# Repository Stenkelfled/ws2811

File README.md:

# ws2811
WS2811 LED microcontroller driver with USB-connection and UserInterface for PC

Another Project for a WS2811 LED-strip. The clue here is, that the controller board is accessible via USB and that you can control the LEDs from you PC/Laptop.

Includes:
- Electronics design with ATXMEGA
- code for the xmega
- an UserInterface for a pc to communicate with the microcontroller written with Qt

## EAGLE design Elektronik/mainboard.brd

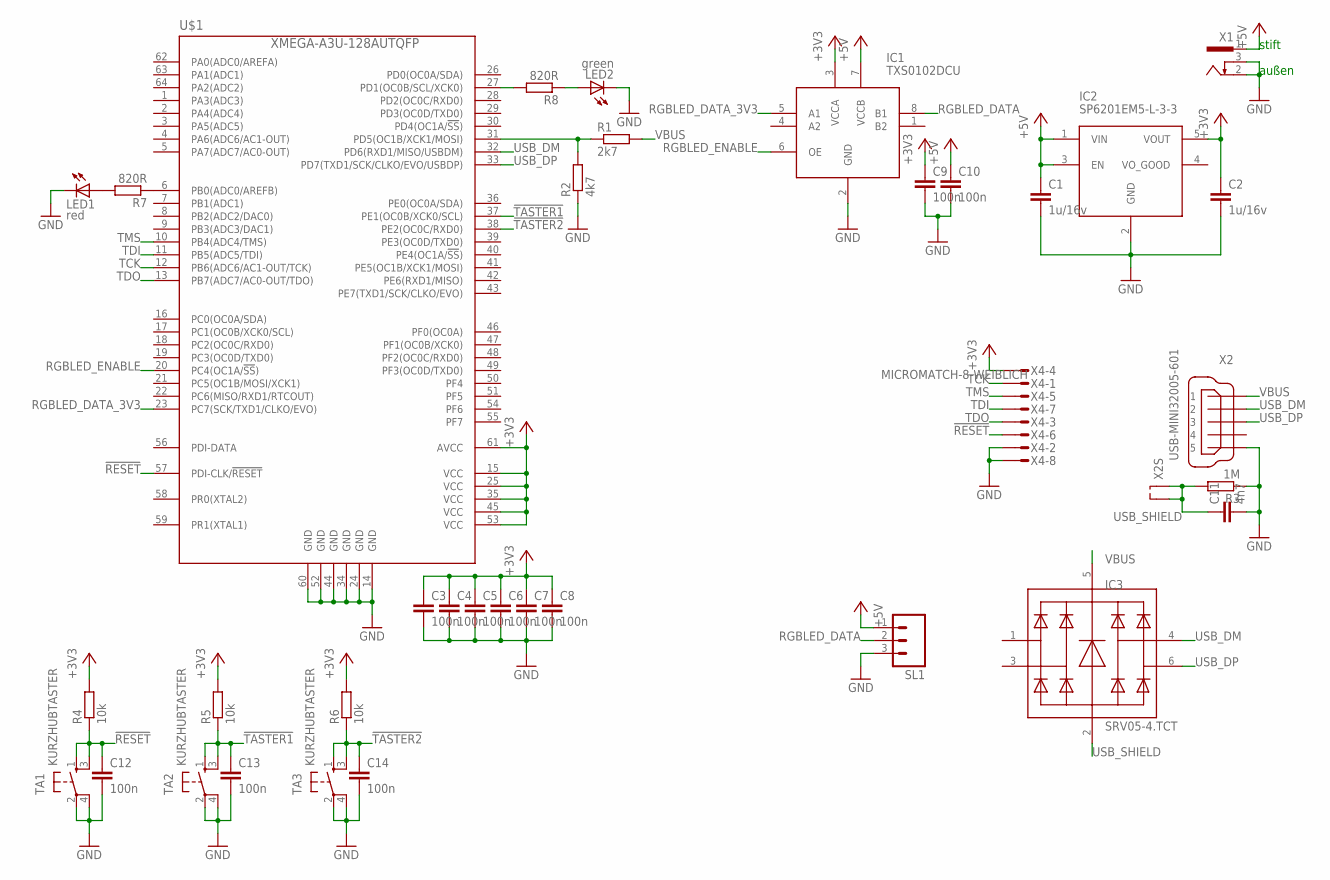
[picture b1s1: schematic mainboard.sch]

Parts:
C1, C2: 1u/16v; C0603
C3, C4, C5, C6, C7, C8, C9, C10, C12, C13, C14: 100n; C0603
C11: 4n7; C0603
IC1: TXS0102DCU; DCU8
IC2: SP6201EM5-L-3-3; SOT23-5
IC3: SRV05-4.TCT; SOT23-6
LED1: red; CHIPLED_0603
LED2: green; CHIPLED_0603
R1: 2k7; R0603
R2: 4k7; R0603
R3: 1M; R0603
R4, R5, R6: 10k; R0603
R7, R8: 820R; R0603
SL1: M03; 03P
TA1, TA2, TA3: KURZHUBTASTER; TA93XX
U$1: XMEGA-A3U-128AUTQFP; TQFP64
X1: 733980-62
X2: USB-MINI32005-601; 32005-601
X4: MICROMATCH-8-WEIBLICH; MICROMATCH-8

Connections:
!RESET!: C12.1, R4.1, TA1.1 (S), TA1.3 (S1), U$1.57 (PDI-CLK/!RESET), X4.6
!TASTER1!: C13.1, R5.1, TA2.1 (S), TA2.3 (S1), U$1.37 (PE1(OC0B/XCK0/SCL))
!TASTER2!: C14.1, R6.1, TA3.1 (S), TA3.3 (S1), U$1.38 (PE2(OC0C/RXD0))
+3V3: C2.1, C3.1, C4.1, C5.1, C6.1, C7.1, C8.1, C9.1, IC1.3 (VCCA), IC2.5 (VOUT), R4.2, R5.2, R6.2, U$1.15 (VCC), U$1.25 (VCC), U$1.35 (VCC), U$1.45 (VCC), U$1.53 (VCC), U$1.61 (AVCC), X4.4
+5V: C1.1, C10.1, IC1.7 (VCCB), IC2.1 (VIN), IC2.3 (EN), SL1.1, X1.1
GND: C1.2, C2.2, C3.2, C4.2, C5.2, C6.2, C7.2, C8.2, C9.2, C10.2, C11.2, C12.2, C13.2, C14.2, IC1.2 (GND), IC2.2 (GND), LED1.C, LED2.C, R2.1, R3.1, SL1.3, TA1.2, TA1.4 (P1), TA2.2, TA2.4 (P1), TA3.2, TA3.4 (P1), U$1.14 (GND), U$1.24 (GND), U$1.34 (GND), U$1.44 (GND), U$1.52 (GND), U$1.60 (GND), X1.2, X1.3, X2.5, X4.2, X4.8
unnamed: R1.1, R2.2, U$1.31 (PD5(OC1B/XCK1/MOSI))
unnamed: R7.1, U$1.6 (PB0(ADC0/AREFB))
unnamed: LED1.A, R7.2
unnamed: R8.2, U$1.27 (PD1(OC0B/SCL/XCK0))
unnamed: LED2.A, R8.1
RGBLED_DATA: IC1.8 (B1), SL1.2
RGBLED_DATA_3V3: IC1.5 (A1), U$1.23 (PC7(SCK/TXD1/CLKO/EVO))
RGBLED_ENABLE: IC1.6 (OE), U$1.20 (PC4(OC1A/!SS!))
TCK: U$1.12 (PB6(ADC6/AC1-OUT/TCK)), X4.1
TDI: U$1.11 (PB5(ADC5/TDI)), X4.7
TDO: U$1.13 (PB7(ADC7/AC0-OUT/TDO)), X4.3
TMS: U$1.10 (PB4(ADC4/TMS)), X4.5
USB_DM: IC3.4 (3), U$1.32 (PD6(RXD1/MISO/USBDM)), X2.2
USB_DP: IC3.6 (4), U$1.33 (PD7(TXD1/SCK/CLKO/EVO/USBDP)), X2.3
USB_SHIELD: C11.1, IC3.2 (A), R3.2, X2.M1 (S1), X2.M2 (S2)
VBUS: IC3.5 (K), R1.2, X2.1

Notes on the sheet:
stift
außen

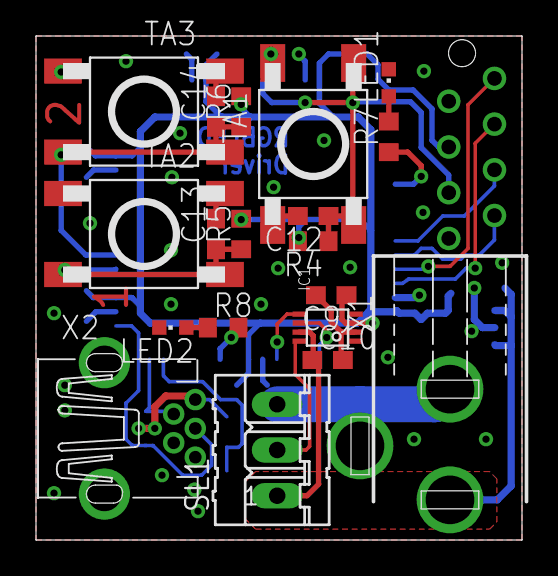
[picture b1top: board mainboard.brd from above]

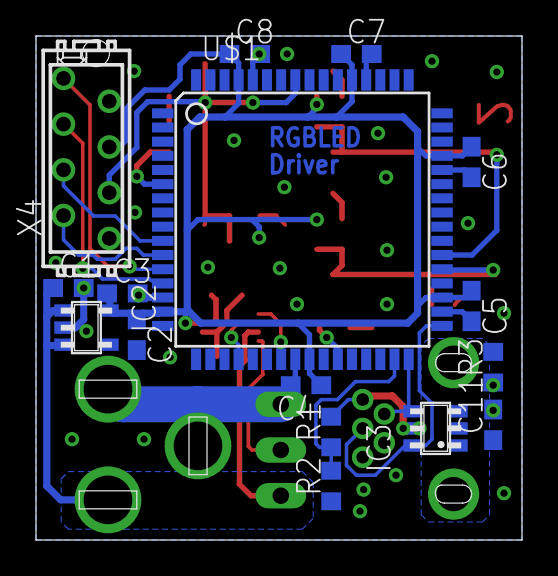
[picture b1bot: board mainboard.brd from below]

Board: 2 copper layers, 27.0 x 28.0 mm, 35 parts (16 on the bottom side), 22 nets.

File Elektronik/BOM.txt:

Menge |Wert                  |Bauelement            |Package      |FARNELL |REICHELT    |DIGIKEY |WUERTH          |Beschreibung                                          |Bauteile                             |
-----------------------------------------------------------------------------------------------------------------------------------------------------------------------------------------------------------------
1     |                      |                      |             |        |MM SL 8SK   |        |                |                                                      |X4                                   |
1     |                      |                      |             |        |PSK 254/3W  |        |                |                                                      |SL1                                  |
1     |                      |733980-62             |733980-62    |        |HEBW 21     |        |                |FEMALE PRINT CONNECTOR                                |X1                                   |
1     |                      |M03                   |03P          |        |PSS 254/3G  |        |                |AMP QUICK CONNECTOR                                   |SL1                                  |
1     |1M                    |R-EU_R0603            |R0603        |1469746 |            |        |                |RESISTOR, European symbol                             |R3                                   |
2     |1u/16v                |C-EUC0603             |C0603        |1463388 |            |        |                |CAPACITOR, European symbol                            |C1,C2                                |
1     |4n7                   |C-EUC0603             |C0603        |1865543 |            |        |                |CAPACITOR, European symbol                            |C11                                  |
3     |10k                   |R-EU_R0603            |R0603        |1469748 |            |        |                |RESISTOR, European symbol                             |R4,R5,R6                             |
1     |27k                   |R-EU_R0603            |R0603        |1627786 |            |        |                |RESISTOR, European symbol                             |R1                                   |
1     |47k                   |R-EU_R0603            |R0603        |1692459 |            |        |                |RESISTOR, European symbol                             |R2                                   |
11    |100n                  |C-EUC0603             |C0603        |1759122 |            |        |                |CAPACITOR, European symbol                            |C3,C4,C5,C6,C7,C8,C9,C10,C12,C13,C14 |
2     |820R                  |R-EU_R0603            |R0603        |1469841 |            |        |                |RESISTOR, European symbol                             |R7,R8                                |
3     |KURZHUBTASTER         |KURZHUBTASTER         |TA93XX       |        |Taster 9314 |        |430 182 043 816 |                                                      |TA1,TA2,TA3                          |
1     |MICROMATCH-8-WEIBLICH |MICROMATCH-8-WEIBLICH |MICROMATCH-8 |        |MM FL 8G    |        |                |MicroMaTch 8  7-215464-8 / 0-215464-8                 |X4                                   |
1     |SP6201EM5-L-3-3       |SP6201EM5-L-3-3       |SOT23-5      |9388184 |            |        |                |Linearregler                                          |IC2                                  |
1     |SRV05-4.TCT           |SRV05-4.TCT           |SOT23-6      |1456415 |            |        |824001          |SRV05-4.TCT bzw. WE-TVS TVS Diode  High Speed Series |IC3                                  |
1     |TXS0102DCU            |TXS0102DCU            |DCU8         |1703315 |            |        |                |I2C/UART-Levelshifter                                 |IC1                                  |
1     |USB-MINI32005-601     |USB-MINI32005-601     |32005-601    |        |USB BWM     |        |                |MINI USB-B R/A DIP 5pol.                              |X2                                   |
1     |XMEGA-A3U-128AUTQFP   |XMEGA-A3U-128AUTQFP   |TQFP64       |2066298 |            |        |                |Atmel XMega A3 series processor                       |U$1                                  |
1     |green                 |LEDLGCHIPLED_0603     |CHIPLED_0603 |        |LG L29K     |        |                |LED                                                   |LED2                                 |
1     |red                   |LEDLRCHIPLED_0603     |CHIPLED_0603 |        |LS L29K     |        |                |LED                                                   |LED1                                 |

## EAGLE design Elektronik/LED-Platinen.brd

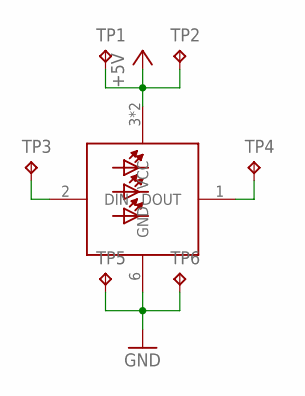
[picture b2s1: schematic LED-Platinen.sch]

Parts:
TP1, TP2, TP3, TP4, TP5, TP6: TPTP15SQ; TP15SQ
U$1: RGBLED

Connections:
+5V: TP1.TP, TP2.TP, U$1.3 (VCC), U$1.5 (VCC)
unnamed: TP4.TP, U$1.1 (DOUT)
unnamed: TP3.TP, U$1.2 (DIN)
RM: TP5.TP, TP6.TP, U$1.6 (GND)

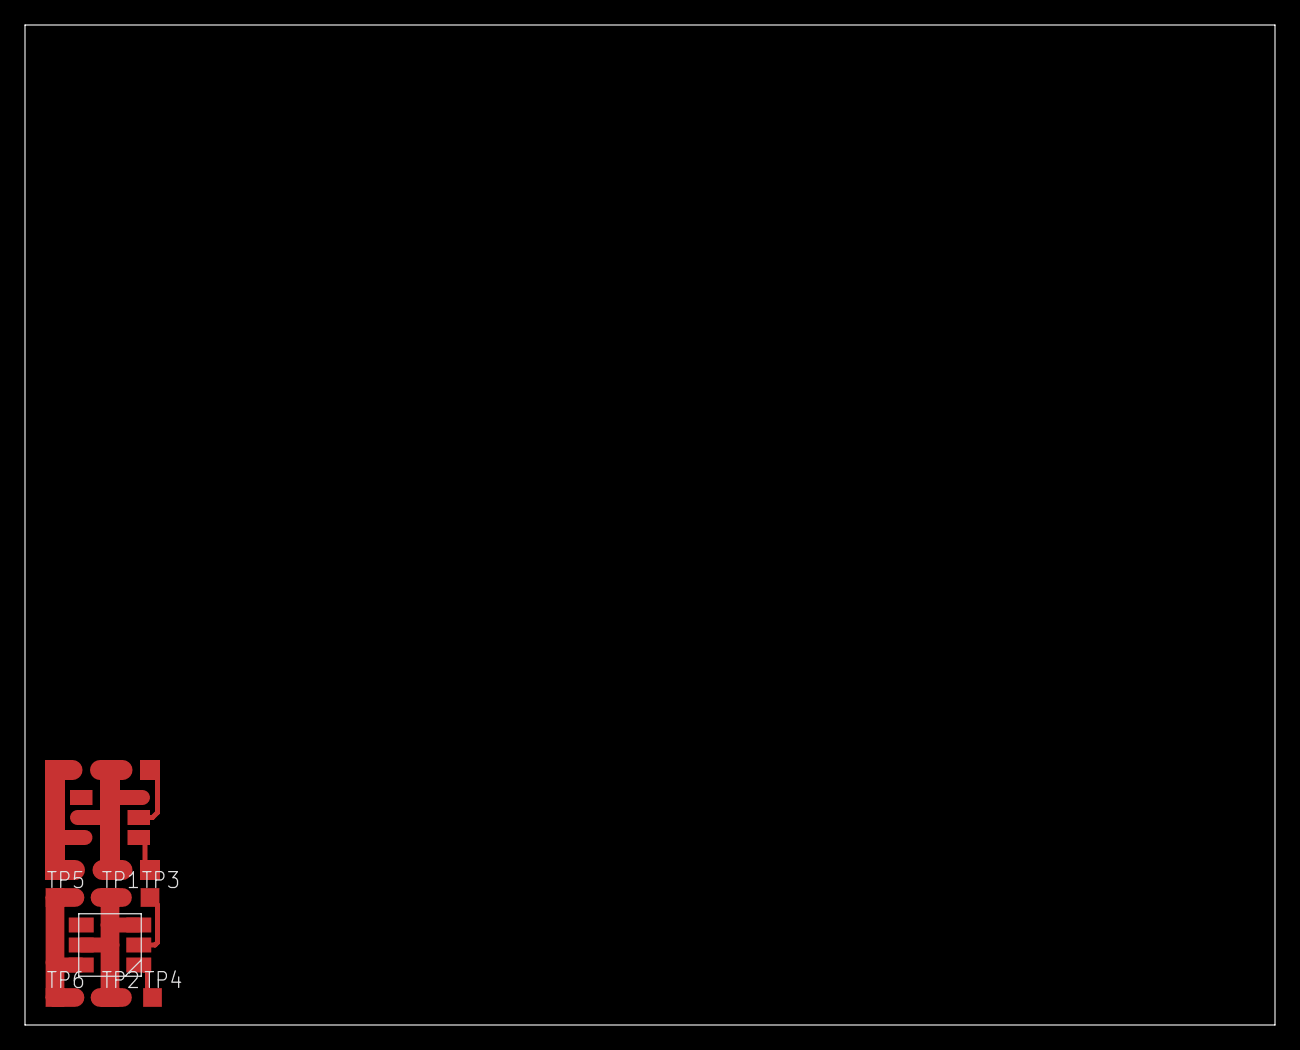
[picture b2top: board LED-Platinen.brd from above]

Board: 2 copper layers, 100.0 x 80.0 mm, 7 parts (0 on the bottom side), 4 nets.

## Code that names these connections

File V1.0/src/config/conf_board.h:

/**
 * \file
 *
 * \brief User board configuration template
 *
 */

#ifndef CONF_BOARD_H
#define CONF_BOARD_H

#define LED_GN				IOPORT_CREATE_PIN(PORTD,1)
#define LED_GN_ON			ioport_set_pin_level(LED_GN,true);
#define LED_GN_OFF			ioport_set_pin_level(LED_GN,false);
#define LED_RD				IOPORT_CREATE_PIN(PORTB,0)
#define LED_RD_ON			ioport_set_pin_level(LED_RD,true);
#define LED_RD_OFF			ioport_set_pin_level(LED_RD,false);

/*#define TASTER1				IOPORT_CREATE_PIN(PORTE,1)
#define TASTER2				IOPORT_CREATE_PIN(PORTE,2)*/

#define VBUS				IOPORT_CREATE_PIN(PORTD,5)

#define RGBLED_ENABLE_PIN	IOPORT_CREATE_PIN(PORTC,4)
#define RGBLED_ENABLE_TX	ioport_set_pin_level(RGBLED_ENABLE_PIN,true);
#define RGBLED_DISABLE_TX	ioport_set_pin_level(RGBLED_ENABLE_PIN,false);
#define RGBLED_DATA_PIN		IOPORT_CREATE_PIN(PORTC,7)

#endif // CONF_BOARD_H

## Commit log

2014-01-11 * Initial Commit. * added ASF for SystemClock and IOs * added Initialization for SystemClock and IOs
2014-01-11 * Ich brauche keine Debug- und Binärdateien in meinem Repo...
2014-01-11 * die Debugdateien werden ab jetzt ignoriert
2014-01-11 * Macros zum ein- und ausschalten der LEDs und des Levelshifters
2014-01-11 * ...da hat git die nachträglichen Änderungen doch nicht mitgenommen :(
2014-02-22 Schaltplan und Layout hinzugefügt
2014-03-22 * Initialisierung für DMA und UASRT in SPI-MODE. mal sehen...
2014-03-22 * mal sehen, ob der DMA was rausschiebt...
2014-03-22 * Puffer füllen hinzugefügt - jetzt fehlt das Testen
2014-03-22 * Kommentar: aufpassen beim testen ;)
2014-04-08 * clock and io settings are now working
2014-04-25 *Led-Ansteuerung in master branch hinzugefügt
2014-04-25 *Kompilierfehler beseitigt
2014-04-25 *nutzloses ADC-Projekt entfernt
2014-04-25 * merge from generate_led_buffer to master
2014-04-26 * LED-Bitreihenfolge korrigiert
2014-04-26 * was vergessen
2014-04-26 * neue Sende- und Resetfunktion für die LEDs
2014-04-27 * Anfang für eine EURO-Platine mit LED-Footprints
2014-04-27 * nächster Test vorbereitet
2014-04-29 * kleine Änderung vor branchwechsel
2014-04-29 * on-board-leds mit eingebunden
2014-04-29 *LED leuchtet jetzt
2014-04-29 * Senden ohne unnötige Wartezeiten---wenn der Sendevorgang abgeschlossen ist, dann ist auch schluss
2014-04-30 * standartmäßig datenleitung auf low. *TODO: gucken, dass am Anfang vom Senden die Datenleitung nicht zu lange high ist
2014-05-01 * SO. Jetzt wird auch die gewählte Farbe richtig angezeigt. Lösung war, die gesamte Zeit einfach nur 0 zu senden (also Leitung ständig Low halten). Wird im Moment per DMA gemacht, weil der UART beim 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
2014-05-01 * RGB-HSV-Konvertierung hinzugefügt * PROBLEM: die LED flackert
2014-05-04 * DMA-CH1 ausschalten, bevor DMA-CH0 eingeschaltet wird --> Jetzt leuchtet sie schön gleichmäßig - ohne hässliches Blitzen
2014-05-04 * Europlatine mit 60 Footprints zum anschließen
2014-05-04 * altes Zeug gelöscht
2014-05-07 * bisschen ausgemistet * schnelles Farbe setzen hinzugefügt * Buttons in Betrieb genommen
2014-06-09 nicht benötigtes ASF-zeug gelöscht
2014-06-10 EEPROM schreiben (seitenweise) scheint zu funktionieren
2014-06-15 auf 3 LEDs umgestellt
2014-06-28 [USB-Driver]zumindest das Enumerieren funktioniert jetzt mit dem ASF-Treiber. Referenzimplementierung hinzugefügt, aber die ist eigenlich nicht mehr nötig
2014-06-28 Beispielcode zum Senden und Empfangen von Daten (gaaanz einfach)
2014-06-28 [USB-Driver] Erkennung der Power-line - funktioniert aber hardwaremäßig noch nicht so gut, weil die Datenleitungen die Powerline hochziehen
2014-07-01 [Elektronik] Spannungsteiler für VBUS angepasst, damit die Pullups der Datenleitungen die VBUS-leitung nicht über die ESD-Dioden nach oben ziehen
2014-07-01 [USB-driver] Der Treiber ist jetzt interruptbasiert und wartet auf eine Präambel, bevor er Daten annimmt
2014-07-02 Auswertung für die USB-Daten angefangen. Kompliliert, ist aber noch nicht getestet
2014-07-07 * Debugausgaben per USB juhuuu * Statemachinekernel läuft auch - nur die Statemachine an sich ist noch nicht bugfrei
2014-07-07 Die LEDs leuchten per USB-Ansteuerung
2014-07-07 * debugpuffer-probleme behoben. * Leds leuchten bei RGB (0xFF 0xFF 0xFF) nicht mehr. Vielleicht ist die Austastlücke zu kurz?
2014-08-03 Anfänge für das UI mit QT. Zumindest der serielle Port funktioniert schon
2014-08-03 bisschen spät für einen commit, daher ist das Log nicht so zuverlässig: wahrscheinlich das USB-Debug verbessert und die Auswertung der USB-Daten erweitert
2014-08-03 Protokoll verfeinert
2014-08-03 UI mit python. wird nicht weiterverfolgt
2014-08-03 Datei vergessen
2014-08-04 GraphicsView hinzugefügt und auch schon den ersten Prototyp für die LED-Darstellung
2014-08-05 [LUI] Verbereitungen, um die LedItems gruppieren zu können
2014-08-05 Gruppe kann jetzt Leds enthalten. Die Positionierung der Gruppen funktoniert noch nicht
2014-08-05 Events kommen jetzt an - aber dafür gibts kein QGraphicsItemGroup mehr, sondern das GroupItem managt das jetzt
2014-08-09 Items sind jetzt alle selectable
2014-08-10 [LUI] Led von Gruppe entfernen geht. -> das muss auch bei mittleren Leds sichtbar werden; leere Gruppen müssen entfernt werden
2014-08-11 [LUI] gruppieren und Gruppierung auflösen geht. Jetzt noch Markieren, indem man ein Viereck zieht
2014-08-12 [LUI]* Verschieben von Leds und Gruppen funktioniert, Gruppenhintergrund wird dann auch erweitert * Auswahl von Leds intuitiver gemacht
2014-08-12 [LUI] Auswahl jetzt auch mit Rechteck
2014-08-13 [LUI]* zoom mit Mausrad hinzugefügt * Farbauswahl eingefügt, aber im Moment noch keine Funktionalität
2014-08-13 [LUI] aktuelle Farben der Items werden angezeigt
2014-08-13 [LUI] Farbe setzen für Leds funktioniert, inkl. Helligkeit einstellen - bis auf die benutzerdefinierte Farbe.
2014-08-13 [LUI] rename stuff
2014-08-13 [LUI] Farbauswahl jetzt auch mit benutzerdefinierter Farbe
2014-08-17 [LUI] Testfunktion für die Farbe
2014-08-17 [all] Farbtest funktioniert
2014-08-17 [LUI] Puffer für USB-Daten [AVR] Auswertung der USB-Daten ohne evaluator, weil einfacher geworden und der Evaluator wird später noch benötigt
2014-08-17 [LUI] Bug in der Farbgebung behoben
2014-08-17 [LUI] *Begonnen mit der Gruppendefinitionen fürs USB * Item-Casts sauberer gemacht
2014-08-17 [LUI] Auch wenn die gleiche Farbe rauskommt, ist HSV leider nicht gleich RGB
2014-08-17 [LUI] Beim Gruppieren wird jetzt die Reihenfolge der LEDs beachtet. Hat allerdings im Moment den Nachteil, dass man die Leds nicht mehr verschieben kann.
2014-08-18 [LUI] angezeigten VALUE der Farben so korrigiert, dass auch bei niedrigem originalem VALUE noch die Farbe zu sehen ist
2014-08-18 [LUI] Blöde Kommentare gelöscht
2014-08-19 [LUI]* Leds kennen ihre Position in der Gruppe * Gruppenhintergrund vergrößert sich, wenn eine LED bewegt wird
2014-09-02 [LUI] Drag&Drop für die Leds vorbereitet. Leider schnipsen die nach dem drop noch nicht an die gewünschte Position
2014-09-03 [LUI] Die Leds schnipsen nicht mehr(aber ich weiß nicht richtig, warum - ich hab nur die Propagation von mouseMoveEvent entfern). Stilisierte Led beim verschieben.
2014-09-05 [LUI] Verschieben innerhalb der Gruppe funktioniert. Jetzt noch DropEnter und DropLeave
2014-09-06 [LUI] drag und drop für die ledscene. scheiß gemache
2014-09-06 [LUI] endlich funktionieren die Events (wieder) so, wie sie sollen. Jetzt nur noch Leben rein...
2014-09-06 [LUI]das Auswahlrechteck verschönert. Jetzt mit gestricheltem Rand und halbtransparenter Fläche
2014-09-07 [LUI] endlich funktioniert das Verschieben mit den Gruppen
2014-09-09 [LUI] erzeugung des bytecodes für die Gruppendefinition angepasst
2014-09-09 [LUI] oller Eventnachbau in der Scene. Jetzt funktioniert auch das Verschieben der Leds innerhalb von Gruppen, die nich auf (0,0) liegen wieder
2014-09-10 [LUI] Vorbereitungen zum Speichern und lesen
2014-09-10 [LUI] Speichern und laden funktioniert (bis jetzt)
2014-09-10 [LUI] überflüssige Debugausgaben entfernt
2014-09-10 [LUI] Gruppen haben nun Namen, die in der Statusleiste angezeigt werden
2014-09-11 [LUI] Kontextmenu für die Gruppen hinzugefügt. Man kann ihnen jetzt Namen geben und die Anordnung zwischen horizontal und vertikal umschalten
2014-09-24 [LUI] Splitter eingefügt
2014-10-07 [LUI] jetzt gibt es schon Gruppen für die Sequenzen.
2014-10-07 [LUI] wichtiger Nachtrag: jetzt werden beim löschen der Listeneiträge auch deren Pointer gelöscht
2014-10-14 [LUI] weiter an der Sequenzansicht
2014-10-14 [LUI] Sequenceitems werden jetzt standardmäßig für jede Gruppe erzeugt - tun aber noch nichts
2014-10-14 [LUI] Größe der sequenceitems angepasst
2014-10-15 [LUI] Verbindungen zwischen dem ColorDisplay bzw. ColorSelector und den Gruppen deaktiviert
2014-10-23 [LUI] Cursor für die Sequenzen eingefügt. Passt sich auch schon automatisch an verschiedene Gruppenanzahlen an, funktioniert aber noch nicht
2014-10-24 [LUI] Cursor mit Leben gefüllt. Außerdem können den SequenceItems jetzt Farben zugewiesen werden, die auch in der Gruppe angezeigt werden.
2014-10-24 [LUI] wenn eine neue Gruppe erzeugt wird, hat die eine Standardfarbe - und die wird bitteschö
2014-10-24 [LUI] waehrend des Farbe Testens sollen die Leds nicht veraendert werden
2014-10-24 [LUI] jetzt sind auch mehrere SequenceItems möglich. Tabs werden gewechselt, wenn Gruppe oder Item angeklickt wird
2014-10-29 [LUI] Sequenceitems werden nicht mehr deaktiviert, wenn der Cursor verschoben wird
2014-10-29 [LUI] die USB-Daten werden korrekt erzeugt
2014-10-29 [LUI] die USB-Kommandos werden jetzt auch abgesendet
2014-10-29 [uC] Daten von USB in den EEPROM schreiben...
2014-10-29 [LUI] offset für die Gruppenadressen korrigiert
2014-10-29 [uC] eeprom verwaltet jetzt Read- und Write-access
2014-10-30 [uC] das Schreiben des EEPROMs funktioniert
2014-10-30 [uC] es leuchtet
2014-10-30 [LUI] Eine Adresse besteht aus 2Byte
2014-10-30 [uC] es gab Probleme, wenn noch alte Daten im EEPROM standen
2014-10-31 [uC] empfangene Daten werden jetzt im EEPROM abgschlossen, um Konflikte mit bereits bestehenden Daten zu vermeiden
2014-10-31 [LUI] Fehlermeldung, wenn COM nicht geöffnet werden konnte
2014-10-31 [uC] FIX: eine einzelne LED in der Gruppe war bisher nicht möglich
2014-10-31 HOTFIX: man kann im LUI mehr Gruppen anlegen, als der uC versteht. FIX: es gibt jetzt so viele Gruppen, wie LEDs, aber das funktioniert auf Dauer nicht
2014-12-02 [Elektronik] Layout für Fertigung in der Uni angepasst
2015-01-27 [Elektronik] Anfänge für neue Streifenplatinen
2015-01-27 verschiedenes
2015-01-27 Bom-Dateien bitte ignorieren!
2015-03-16 [Elektronik] altes Zeug entfernt
2015-03-16 Python UserInterface ist obsolete
2015-03-16 Deleted unused usb-libraries
2015-03-16 [uC] updated project files for microcontroller
2015-08-27 [gui-doc] Added Doxyfile for GUI. Usage: make qtdoc
2015-08-27 [lui-doc] Die Hilfe wird jetzt angezeigt... Fehlt noch der Inhalt...
2015-08-28 [lui] Ressource file for splitter-styles
2015-08-28 [lui] started to re-organize the lui (no QtDesigner, but adding all stuff in code
2015-08-28 [lui] added first, working DockWidget
2015-08-28 [lui, doc] Automatische Links zur Qt-Doku
2015-08-28 [lui, doc] fixed wrong address to qt-documentation
2015-08-28 [lui, doc] more documentation
2015-11-22 [gui]Fixed compile error
2015-11-22 [gui] removed not used function
2015-11-27 [LUI] no more *.pro.user*-files in the Repo!
2015-11-27 [lui] removed test command
2015-12-04 [gitignore] *.pro.user-files
2015-12-04 [LUI] more documentation
2015-12-04 [LUI] more documentation. Current problem: how to ensure, that no LedItem is removed from the scene by dropping it outside
2016-01-03 New QGraphicsSceneDragDropEvent ensures, that any LED dropped outside its scene will be replaced on an empty spot inside the scene.
2016-01-03 more comments
